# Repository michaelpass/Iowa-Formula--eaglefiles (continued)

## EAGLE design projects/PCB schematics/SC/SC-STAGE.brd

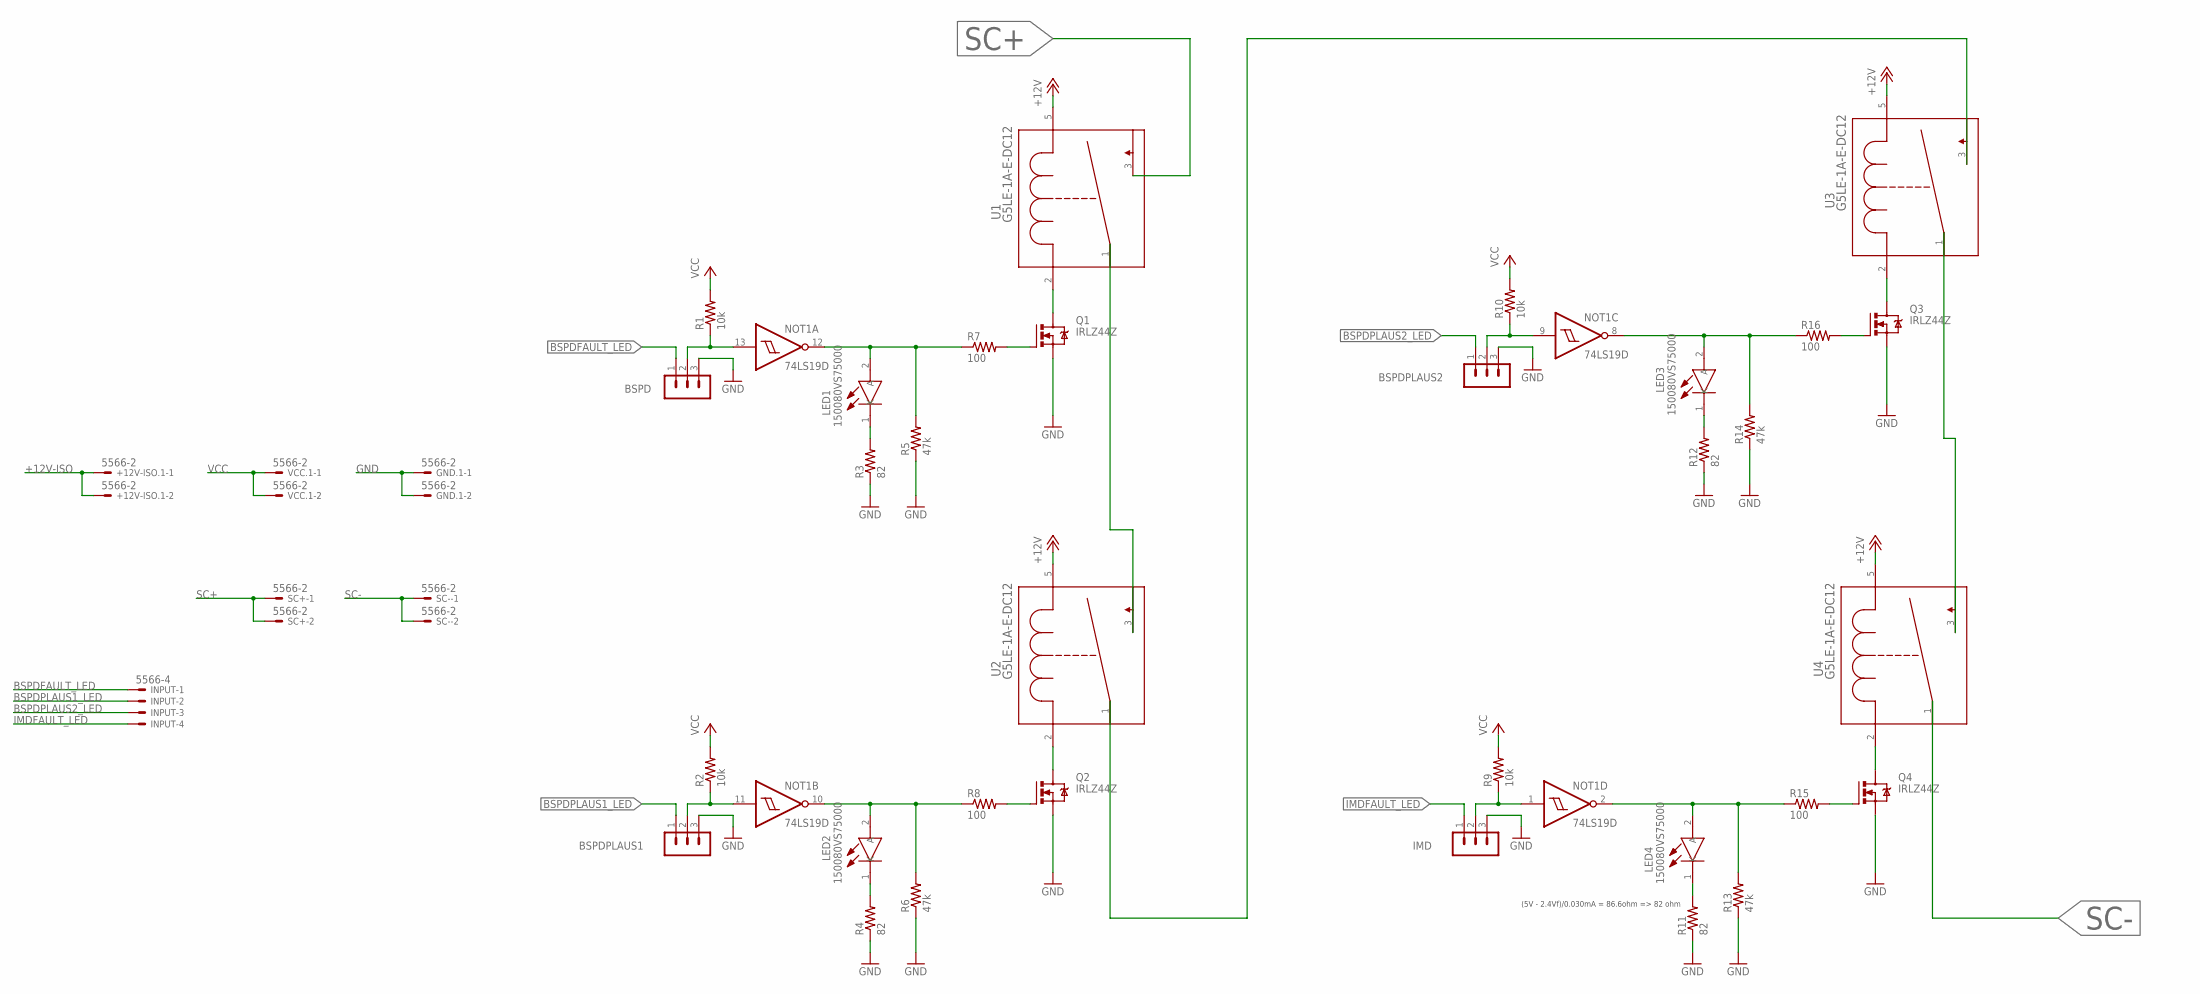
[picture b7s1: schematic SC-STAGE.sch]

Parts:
+12V-ISO.1: 5566-2
BSPD: MA03-1
BSPDPLAUS1, BSPDPLAUS2: MA03-1
GND.1: 5566-2
IMD: MA03-1
INPUT: 5566-4
LED1, LED2, LED3, LED4: 150080VS75000; LEDC2012X80N
NOT1: 74LS19D; SO14
Q1, Q2, Q3, Q4: IRLZ44Z; TO220BH
R1, R2, R9, R10: 10k; R0805
R3, R4, R11, R12: 82; R0805
R5, R6, R13, R14: 47k; R0805
R7, R8, R15, R16: 100; R0805
SC+: 5566-2
SC-: 5566-2
U1, U2, U3, U4: G5LE-1A-E-DC12
VCC.1: 5566-2

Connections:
+12V-ISO: +12V-ISO.1.1, +12V-ISO.1.2, U1.5 (4), U2.5 (4), U3.5 (4), U4.5 (4)
BSPDFAULT_LED: BSPD.1, INPUT.1
BSPDPLAUS1_LED: BSPDPLAUS1.1, INPUT.2
BSPDPLAUS2_LED: BSPDPLAUS2.1, INPUT.3
GND: BSPD.3, BSPDPLAUS1.3, BSPDPLAUS2.3, GND.1.1, GND.1.2, IMD.3, NOT1.7 (GND), Q1.S, Q2.S, Q3.S, Q4.S, R3.1, R4.1, R5.1, R6.1, R11.1, R12.1, R13.1, R14.1
IMDFAULT_LED: IMD.1, INPUT.4
LED4: LED4.1 (K), R11.2
unnamed: Q1.G, R7.2
unnamed: LED1.2 (A), NOT1.12 (O), R5.2, R7.1
unnamed: LED1.1 (K), R3.2
unnamed: Q1.D, U1.2 (1)
unnamed: Q2.G, R8.2
unnamed: LED2.2 (A), NOT1.10 (O), R6.2, R8.1
unnamed: LED2.1 (K), R4.2
unnamed: Q2.D, U2.2 (1)
unnamed: U1.1 (2), U2.3
unnamed: U3.1 (2), U4.3
unnamed: Q4.G, R15.2
unnamed: LED4.2 (A), NOT1.2 (O), R13.2, R15.1
unnamed: Q4.D, U4.2 (1)
unnamed: Q3.G, R16.2
unnamed: LED3.2 (A), NOT1.8 (O), R14.2, R16.1
unnamed: LED3.1 (K), R12.2
unnamed: Q3.D, U3.2 (1)
unnamed: U2.1 (2), U3.3
unnamed: BSPDPLAUS2.2, NOT1.9 (I), R10.1
unnamed: IMD.2, NOT1.1 (I), R9.1
unnamed: BSPDPLAUS1.2, NOT1.11 (I), R2.1
unnamed: BSPD.2, NOT1.13 (I), R1.1
SC+: SC+.1, SC+.2, U1.3
SC-: SC-.1, SC-.2, U4.1 (2)
VCC: NOT1.14 (VCC), R1.2, R2.2, R9.2, R10.2, VCC.1.1, VCC.1.2

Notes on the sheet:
(5V - 2.4Vf)/0.030mA = 86.6ohm => 82 ohm

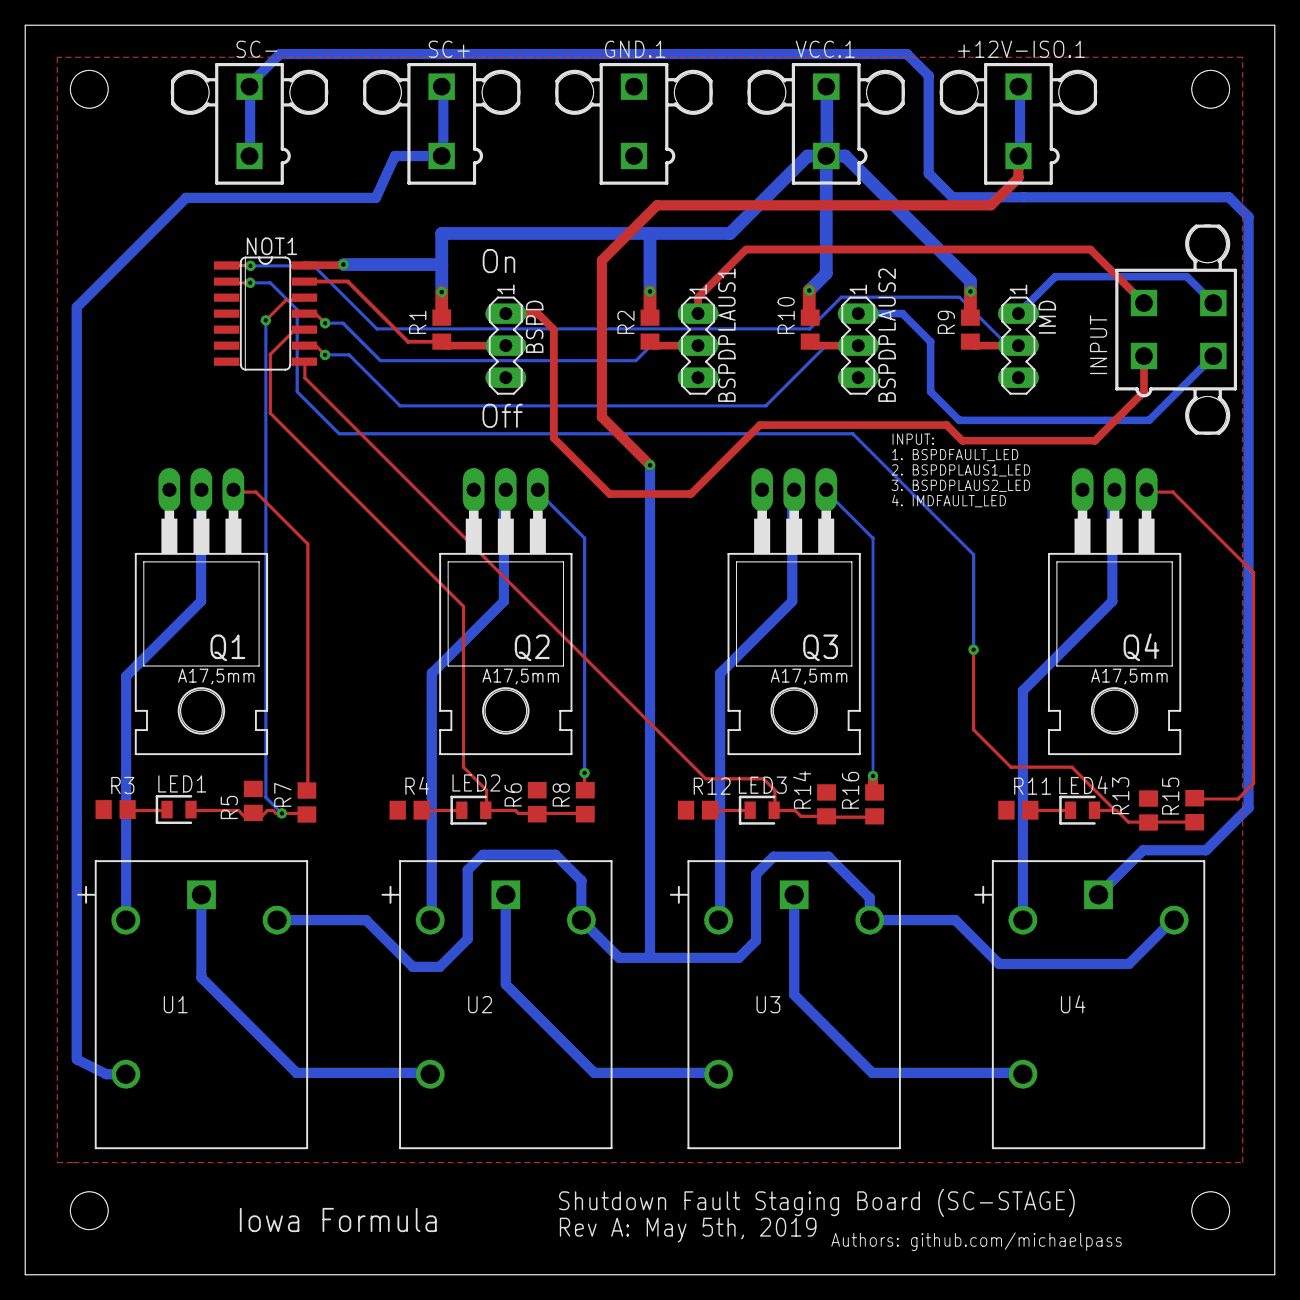
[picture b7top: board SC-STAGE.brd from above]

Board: 2 copper layers, 99.1 x 99.1 mm, 39 parts (0 on the bottom side), 32 nets.

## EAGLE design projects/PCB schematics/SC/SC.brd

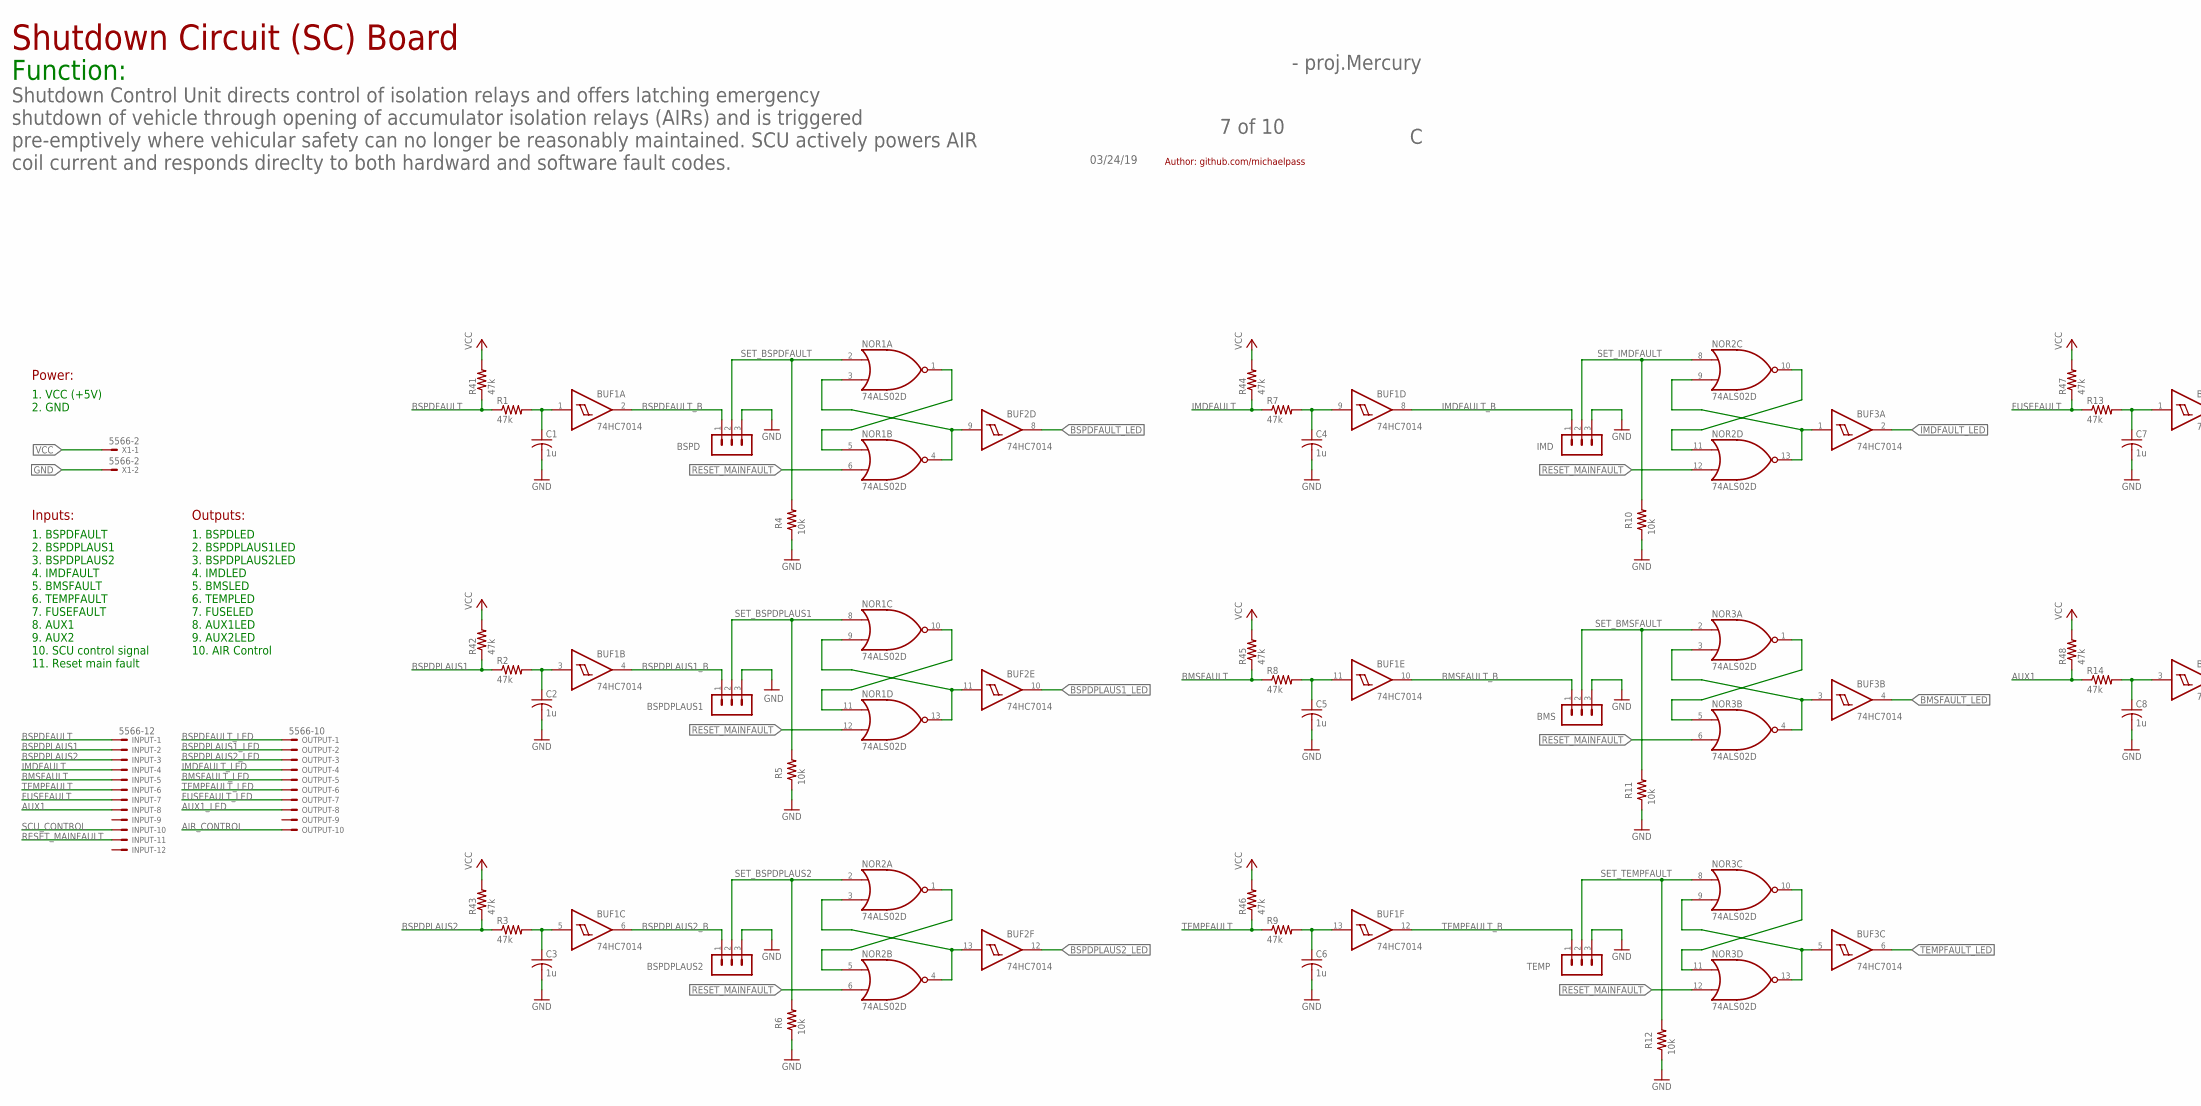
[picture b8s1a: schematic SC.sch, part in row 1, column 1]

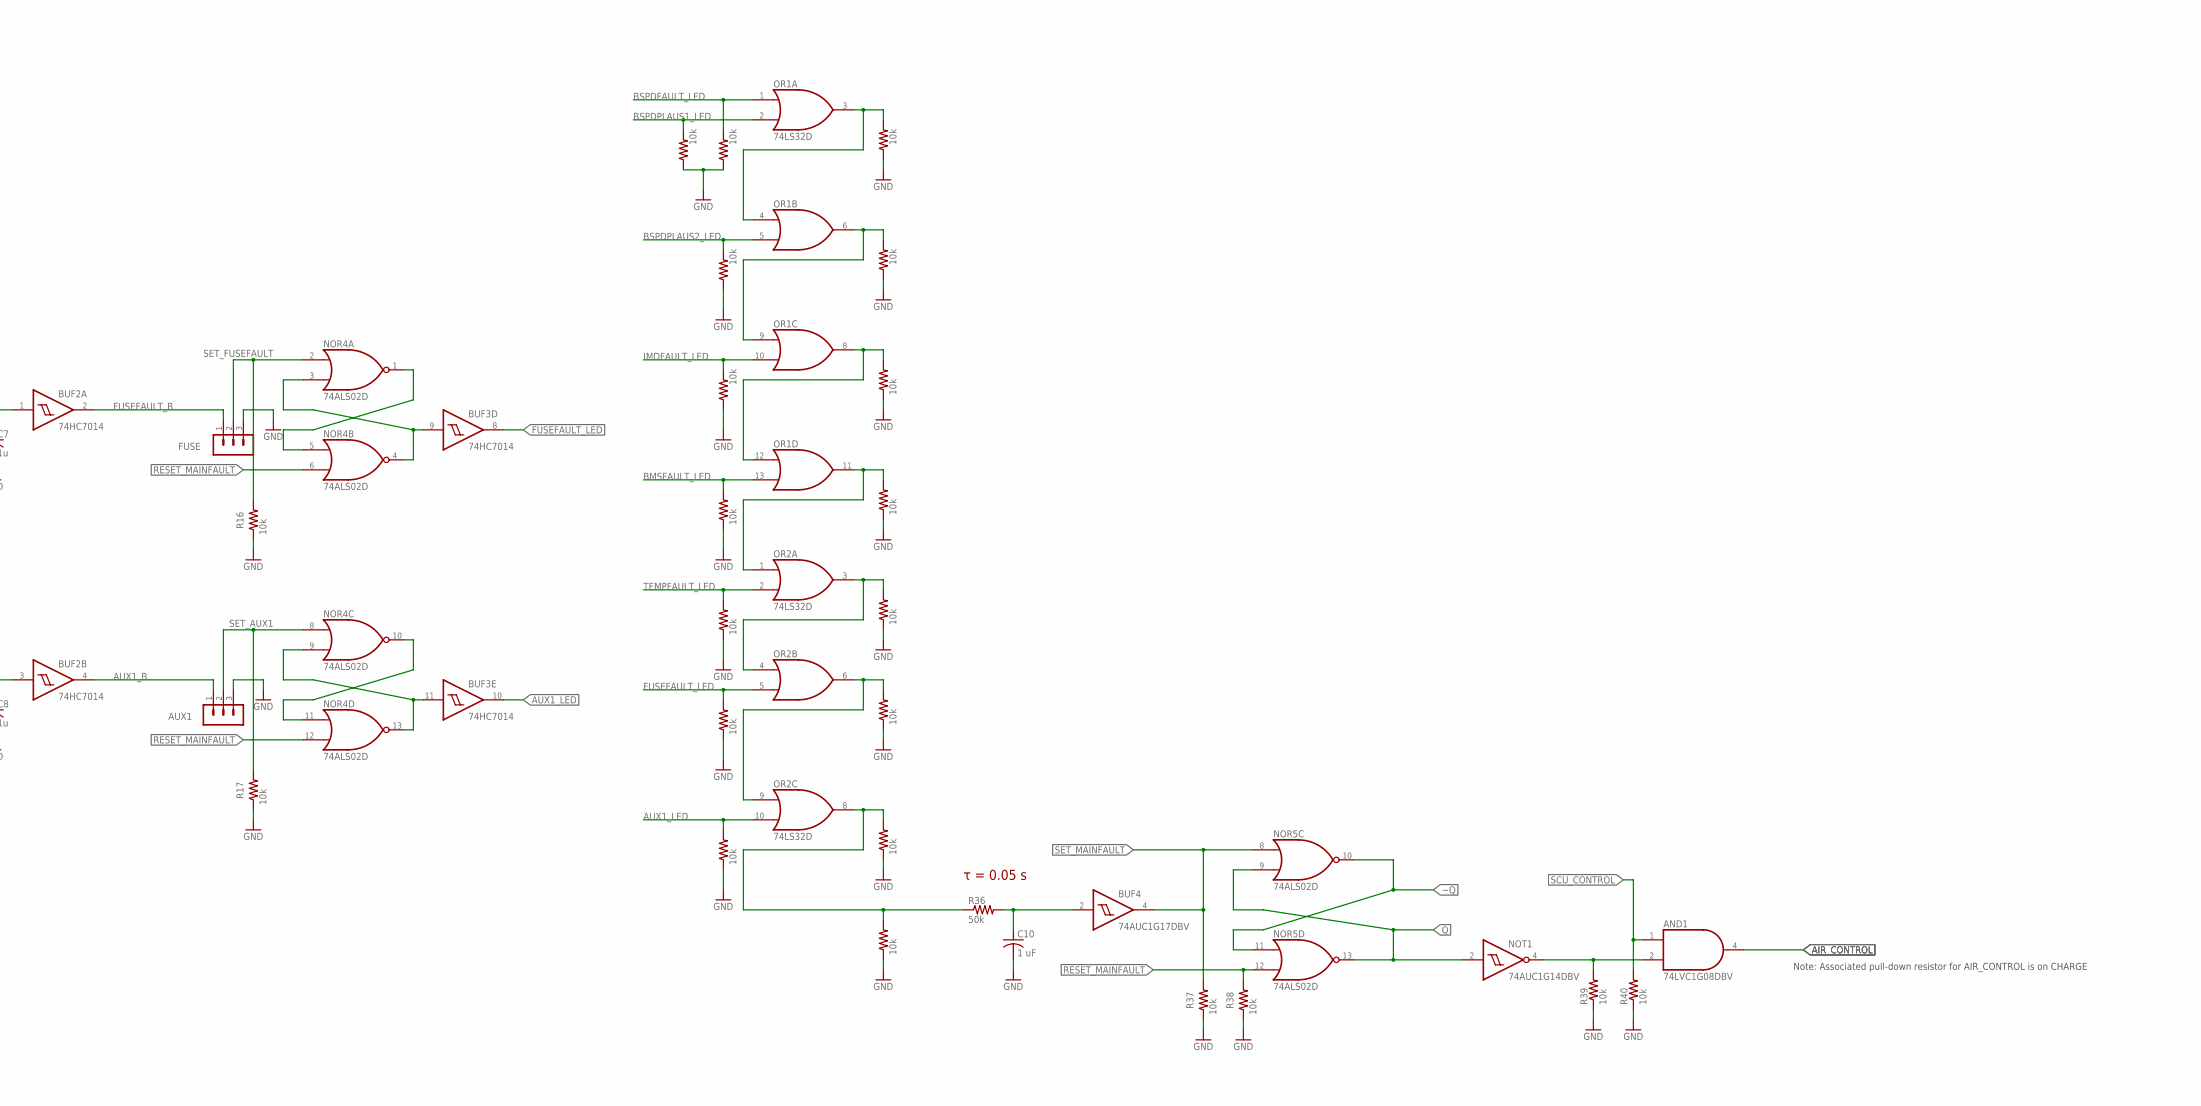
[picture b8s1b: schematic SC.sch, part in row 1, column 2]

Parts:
AND1: 74LVC1G08DBV; SOT23-5
AUX1: MA03-1
BMS: MA03-1
BSPD: MA03-1
BSPDPLAUS1, BSPDPLAUS2: MA03-1
BUF1, BUF2, BUF3: 74HC7014; SO14
BUF4: 74AUC1G17DBV; SOT23-5
C1, C2, C3, C4, C5, C6, C7, C8: 1u; C0805
C10: 1 uF; C0805
FUSE: MA03-1
IMD: MA03-1
INPUT: 5566-12
NOR1, NOR2, NOR3, NOR4, NOR5: 74ALS02D; SO14
NOT1: 74AUC1G14DBV; SOT23-5
OR1, OR2: 74LS32D; SO14
OUTPUT: 5566-10
R1, R2, R3, R7, R8, R9, R13, R14, R41, R42, R43, R44, R45, R46, R47, R48: 47k; R0805
R4, R5, R6, R10, R11, R12, R16, R17, R19, R20, R21, R22, R23, R24, R25, R26, R28, R29, R30, R31, R32, R33, R34, R35, R37, R38, R39, R40: 10k; R0805
R36: 50k; R0805
TEMP: MA03-1
X1: 5566-2

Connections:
AIR_CONTROL: AND1.4 (O), OUTPUT.10
AUX1: INPUT.8, R14.1, R48.1
AUX1_B: AUX1.1, BUF2.4 (O)
AUX1_LED: BUF3.10 (O), OR2.10 (I1), OUTPUT.8, R26.2
BMSFAULT: INPUT.5, R8.1, R45.1
BMSFAULT_B: BMS.1, BUF1.10 (O)
BMSFAULT_LED: BUF3.4 (O), OR1.13 (I1), OUTPUT.5, R23.2
BSPDFAULT: INPUT.1, R1.1, R41.1
BSPDFAULT_B: BSPD.1, BUF1.2 (O)
BSPDFAULT_LED: BUF2.8 (O), OR1.1 (I0), OUTPUT.1, R20.2
BSPDPLAUS1: INPUT.2, R2.1, R42.1
BSPDPLAUS1_B: BSPDPLAUS1.1, BUF1.4 (O)
BSPDPLAUS1_LED: BUF2.10 (O), OR1.2 (I1), OUTPUT.2, R19.2
BSPDPLAUS2: INPUT.3, R3.1, R43.1
BSPDPLAUS2_B: BSPDPLAUS2.1, BUF1.6 (O)
BSPDPLAUS2_LED: BUF2.12 (O), OR1.5 (I1), OUTPUT.3, R21.2
FUSEFAULT: INPUT.7, R13.1, R47.1
FUSEFAULT_B: BUF2.2 (O), FUSE.1
FUSEFAULT_LED: BUF3.8 (O), OR2.5 (I1), OUTPUT.7, R25.2
GND: AND1.3 (GND), AUX1.3, BMS.3, BSPD.3, BSPDPLAUS1.3, BSPDPLAUS2.3, BUF1.7 (GND), BUF2.7 (GND), BUF3.7 (GND), BUF4.3 (GND), C1.2, C2.2, C3.2, C4.2, C5.2, C6.2, C7.2, C8.2, C10.2, FUSE.3, IMD.3, NOR1.7 (GND), NOR2.7 (GND), NOR3.7 (GND), NOR4.7 (GND), NOR5.7 (GND), NOT1.3 (GND), OR1.7 (GND), OR2.7 (GND), R4.1, R5.1, R6.1, R10.1, R11.1, R12.1, R16.1, R17.1, R19.1, R20.1, R21.1, R22.1, R23.1, R24.1, R25.1, R26.1, R28.1, R29.1, R30.1, R31.1, R32.1, R33.1, R34.1, R35.1, R37.1, R38.1, R39.1, R40.1, TEMP.3, X1.2
IMDFAULT: INPUT.4, R7.1, R44.1
IMDFAULT_B: BUF1.8 (O), IMD.1
IMDFAULT_LED: BUF3.2 (O), OR1.10 (I1), OUTPUT.4, R22.2
unnamed: OR2.6 (O), OR2.9 (I0), R33.2
unnamed: OR2.8 (O), R34.2, R35.2, R36.1
unnamed: OR1.3 (O), OR1.4 (I0), R28.2
unnamed: BUF1.3 (I), C2.1, R2.2
unnamed: BUF1.5 (I), C3.1, R3.2
unnamed: BUF4.2 (I), C10.1, R36.2
unnamed: BUF1.9 (I), C4.1, R7.2
unnamed: AND1.2 (I1), NOT1.4 (O), R39.2
unnamed: BUF1.11 (I), C5.1, R8.2
unnamed: BUF1.13 (I), C6.1, R9.2
unnamed: OR1.6 (O), OR1.9 (I0), R29.2
unnamed: OR1.8 (O), OR1.12 (I0), R30.2
unnamed: OR1.11 (O), OR2.1 (I0), R31.2
unnamed: BUF2.1 (I), C7.1, R13.2
unnamed: BUF2.3 (I), C8.1, R14.2
unnamed: OR2.3 (O), OR2.4 (I0), R32.2
unnamed: BUF1.1 (I), C1.1, R1.2
Q: NOR5.9 (I1), NOR5.13 (O), NOT1.2 (I)
Q_AUX1: BUF3.11 (I), NOR4.9 (I1), NOR4.13 (O)
Q_BMSFAULT: BUF3.3 (I), NOR3.3 (I1), NOR3.4 (O)
Q_BSPDFAULT: BUF2.9 (I), NOR1.3 (I1), NOR1.4 (O)
Q_BSPDPLAUS1: BUF2.11 (I), NOR1.9 (I1), NOR1.13 (O)
Q_BSPDPLAUS2: BUF2.13 (I), NOR2.3 (I1), NOR2.4 (O)
Q_FUSEFAULT: BUF3.9 (I), NOR4.3 (I1), NOR4.4 (O)
Q_IMDFAULT: BUF3.1 (I), NOR2.9 (I1), NOR2.13 (O)
Q_TEMPFAULT: BUF3.5 (I), NOR3.9 (I1), NOR3.13 (O)
RESET_MAINFAULT: INPUT.11, NOR1.6 (I1), NOR1.12 (I1), NOR2.6 (I1), NOR2.12 (I1), NOR3.6 (I1), NOR3.12 (I1), NOR4.6 (I1), NOR4.12 (I1), NOR5.12 (I1), R38.2
SCU_CONTROL: AND1.1 (I0), INPUT.10, R40.2
SET_AUX1: AUX1.2, NOR4.8 (I0), R17.2
SET_BMSFAULT: BMS.2, NOR3.2 (I0), R11.2
SET_BSPDFAULT: BSPD.2, NOR1.2 (I0), R4.2
SET_BSPDPLAUS1: BSPDPLAUS1.2, NOR1.8 (I0), R5.2
SET_BSPDPLAUS2: BSPDPLAUS2.2, NOR2.2 (I0), R6.2
SET_FUSEFAULT: FUSE.2, NOR4.2 (I0), R16.2
SET_IMDFAULT: IMD.2, NOR2.8 (I0), R10.2
SET_MAINFAULT: BUF4.4 (O), NOR5.8 (I0), R37.2
SET_TEMPFAULT: NOR3.8 (I0), R12.2, TEMP.2
TEMPFAULT: INPUT.6, R9.1, R46.1
TEMPFAULT_B: BUF1.12 (O), TEMP.1
TEMPFAULT_LED: BUF3.6 (O), OR2.2 (I1), OUTPUT.6, R24.2
VCC: AND1.5 (VCC), BUF1.14 (VCC), BUF2.14 (VCC), BUF3.14 (VCC), BUF4.5 (VCC), NOR1.14 (VCC), NOR2.14 (VCC), NOR3.14 (VCC), NOR4.14 (VCC), NOR5.14 (VCC), NOT1.5 (VCC), OR1.14 (VCC), OR2.14 (VCC), R41.2, R42.2, R43.2, R44.2, R45.2, R46.2, R47.2, R48.2, X1.1
~Q: NOR5.10 (O), NOR5.11 (I0)
~Q_AUX1: NOR4.10 (O), NOR4.11 (I0)
~Q_BMSFAULT: NOR3.1 (O), NOR3.5 (I0)
~Q_BSPDFAULT: NOR1.1 (O), NOR1.5 (I0)
~Q_BSPDPLAUS1: NOR1.10 (O), NOR1.11 (I0)
~Q_BSPDPLAUS2: NOR2.1 (O), NOR2.5 (I0)
~Q_FUSEFAULT: NOR4.1 (O), NOR4.5 (I0)
~Q_IMDFAULT: NOR2.10 (O), NOR2.11 (I0)
~Q_TEMPFAULT: NOR3.10 (O), NOR3.11 (I0)

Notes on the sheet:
τ = 0.05 s
03/24/19
7 of 10
- proj.Mercury
Author: github.com/michaelpass
Function:
Shutdown Control Unit directs control of isolation relays and offers latching emergency shutdown of vehicle through opening of accumulator isolation relays (AIRs) and is triggered pre-emptively where vehicular safety can no longer be reasonably maintained. SCU actively powers AIR coil current and r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
Shutdown Circuit (SC) Board
Inputs:
1. BSPDFAULT 2. BSPDPLAUS1 3. BSPDPLAUS2 4. IMDFAULT 5. BMSFAULT 6. TEMPFAULT 7. FUSEFAULT 8. AUX1 9. AUX2 10. SCU control signal 11. Reset main fault
Outputs:
1. BSPDLED 2. BSPDPLAUS1LED 3. BSPDPLAUS2LED 4. IMDLED 5. BMSLED 6. TEMPLED 7. FUSELED 8. AUX1LED 9. AUX2LED 10. AIR Control
Power:
1. VCC (+5V) 2. GND
Note: Associated pull-down resistor for AIR_CONTROL is on CHARGE

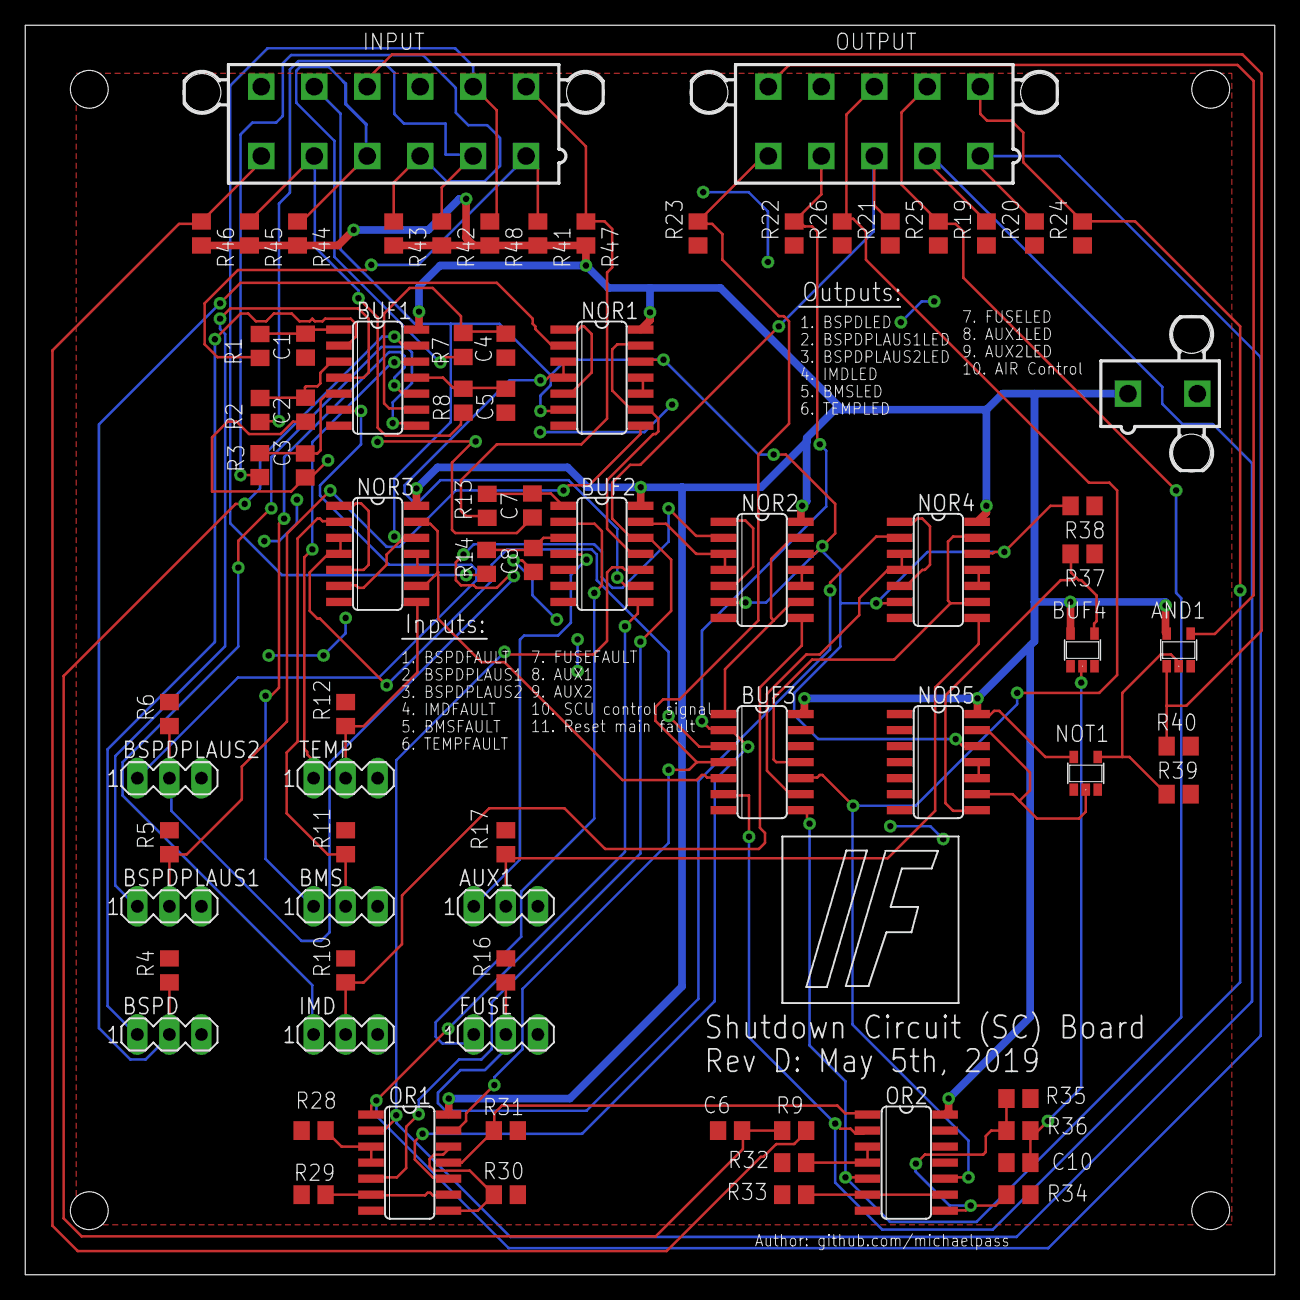
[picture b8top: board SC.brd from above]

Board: 2 copper layers, 99.1 x 99.1 mm, 78 parts (0 on the bottom side), 73 nets.

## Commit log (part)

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2019-02-23 Compatibility revision of .gitignore for cross-platform compatibility. Reset of repo history
2019-04-01 SC - Rev A; First PCB revision complete.
    This marks the first draft of the SC board.
    Parts have been laid out and initial routing completed through
    extensive use of autorouter.
2019-04-01 SC - Added component numbers/names.
    Silkscreen was initially missing component names.
    As many of the original components were resistors/capacitors,
    Values were preferred.
    However, standard board markup convention requires that part numbers
    be given instead.
    Note: Part numbers are given on EAGLE layer tNames, whereas values
2019-04-01 SC - Silkscreen tidy.
    Many silkscreen labels were previously unreadable.
    This commit consisted of moving labels into readable positions
    without as much via obstruction.
2019-04-01 SC - Removed LATCH.
    LATCH board schematic kept around for Electronic Systems Form (ESF)
    All functionality was absorbed through multiple latch circuits added
    through this commit.
2019-04-01 TSMPC - Initial draft (WIP).
    Non-working commit of TSMPC.
    Done simply to show possible board layout.
2019-04-01 PROJ - Deleted duplicate directories.
    $PATH confusion between Windows and POSIX systems lead to multiple nested entries of repository in files. These have been deleted and repo has been consolidated properly.
2019-04-01 SC - Rev C; SC70 -> SOT23.
    For single logic gate components, SC70 was initially chosen.
    These packages proved too small to hand-solder.
    All SC70 packages have been refactored to SOT23.
    SparkFun DRC's added in for additional manufacturability.
2019-04-01 TSALC - Initial build.
    Initial build done by Anshuman.
    TSALC is still WIP.
    TSALC work must be continued on another branch.
2019-04-01 PROJ - Workstation modified files.
    Git history had become polluted with multiple trivial commits.
    Git branching/merging policy will now be followed through GitHub.
    WLS system set up. Anshuman's git history caught up.
    All systems under management have now been merged at this common commit.
2019-04-01 Backlink to CADLAB.io has been added.
2019-04-01 PROJ - Readme modified.
    GitHub is desired to be used as a central project hub for distributing these files.
    Therefore, README.me has been updated to include better explanation of how to install project files. Team logo added to base of repo. TODO: Add to image to GitHub hosting.
2019-04-01 BSPD - Schematic finalized.
    BSPD schematic needed final refactoring for parts.
    Adjustable threshold settings have been put in for plausibility checks
    using resistor arrays.
    Squashed - BSPD - Removed BSPD.brd.
    Too much work will be required to refactor this board.
    It's currently 10 inches long.
2019-04-01 BSPD - Hand routing complete.
    Proceding with auto routing.
    Squashed - BSPD - Initial routing.
    Routing underway. Ground pour chosen. Routing easy choices before attempting autorouting.
2019-04-01 BSPD - Auto-routing complete.
    Performed autorouting. Results generally good. Must correct for ground islands left.
    Must touch up board clearances. BSPD otherwise done.
2019-04-01 BSPD - Rev A; Gerber files.
    Initial board revisions complete. This board represents a working draft. GERBER files have been generated. Please review.
2019-04-02 PROJ - .gitignore includes renumsch.scr
    Whenever the renumber sheet ULP is used, an additional file called renumsch.scr is created. This file occasionally deletes itself, adding unneeded noise to changelog.
2019-04-02 PROJ - Added shorts.lbr.
    Unforunately, EAGLE does not allow for one netlist with multiple names. This is consistent with bringing in two signals together on a PCB, and directly connecting them. There are two solutions for th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
    - Add additional silkscreen and text information to schematic/PCB respectively to show that although there is one common net name for two connectors, they should breakout to different parts of the ci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
    - Use a sort of 'hack' by creating a part which directly shorts on a PCB. This second option produces a more obvious netlist and tidier schematic, but will set off DRC rules checks that must be manua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
    I'll try out the former method to begin with.
    The b
2019-04-02 PROJ - Updated PF1262.lbr
    Previous PF1262.lbr for precharge/discharge resistors was not compatible with ordered Riedon parts.
    Unlike all other TO-126 packages, Riedon's resistors are 2 legged. Upon further inspection, this stated footprint is roughly compatible with the standard TO-126 package, with the middle terminal leg 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
    Two versions of this package were created. One with, and one with/out heatsink.
2019-04-08 PROJ - Renamed library folders. Added con-MATE-N-LOK.
    Custom library files were not showing up upon refresh in EAGLE. The best guess for why this behavior was occuring was that EAGLE only goes one folder deep in looking for matching library names. So, a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
    Additionally, a con-MATE-N-LOK library has been added and will be added on as parts are needed. Please check for commits made on master branch for these.
2019-04-08 PROJ - Added 2P(90deg and vert) connectors to con-MATE lbr.
2019-04-11 PROJ - Arduino-clone.lbr
2019-04-11 PROJ - .gitignore; Added -0 for ignored directories in projects.
2019-04-11 PROJ - .gitignore; Globbing notation fix.
2019-04-11 FUSE - Pull request #4.
    Squash - FUSE - PR#4 changes.
    Minor changes made in trace placement.
2019-04-11 FUSE - Rev A.
    Pull request #4 completed.
    GERBER files for Rev. A created.
2019-04-11 TSMPC - Initial revisions from pull request #3.
    Many changes were needed from Anshuman's initial pull request version. Half of the necessary changes have been made here. Connectors must be added. I believe we should also add in a seperate GND boar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
2019-04-11 TSMPC - Additional revisions for pull request #3.
    Final revisions (apart from connectors and creation of simple GND board) have been done and are ready for review by Anshuman Sahu (and selection of HV connectors)
    Squash - TSMPC - Fixed missing connection as per @rgoedken, PR#3.
    Squash - TSMPC - Added connectors. PR#3 suggestions. Pending approval.
2019-04-11 TSMPC - GLV, Rev A.
    Added in two connectors for chassis connections. X2 goes to TSMP GND connector. Other connector gives 6 access points to ground.
    Squash - TSALC - GLV; Fixed mounting holes.
2019-04-11 TSMPC - Initial revision.
    Completed board, minus the connector. Still needs verification from @michaelpass .
2019-04-11 TSMPC - Rev A.
    Pull request #3 completed.
    GERBER files generated for both TS and GLV boards.
2019-04-11 CHARGE - PR#2 requests made per @rgoedken.
    - Third mosfet added in.
    - Connector expanded to 8 pin
    - AIR+/- added in
    - Short device used to handle connections to power rail
    - 5A fuse added in. 885 makes 5A.
    - 100 ohm gate resistors added into three mosfets.
2019-04-11 CHARGE - Rev A.
    Pull request #2 completed.
    GERBER files created for Rev. A.
2019-04-11 PROJ - EKXF451ELL100MJ20S.lbr.
    Added electrolytic capacitor for 450VDC rated cap.
2019-04-11 TSALC - TS initial revision.
    Squash - TSALC - Added current limited resistors to OK1.
    Squash - TSALC - Hand routing complete.
    GLV components moved over to a separate board with minimal connections left on TS part. Distance explicitly shown on silkscreen. Will require conformal coating to fall in specification.
    All high volt connectors are on the top of the board (vertical connectors chosen, as this will occur outside of accumulator container.)
    Will tidy silkscreen and check for DRC errors.
    Squash - TSALC - Silkscreen additions.
2019-04-11 TSALC - TS; Rev A.
    Adding in silkscreen markings.
    Board has TS and GLV markings separated by 8.26mm. This is the limit imposed by the optocoupler. The rules state that optocouplers are exempt. However, they will likely consider any copper leading up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
    TSALC - TS; Rev A. Pull request #5.
    TSALC boards now ready for pull request review.
2019-04-11 Minor board update
    Cleared up come wiring conflicts
    Board Schematic Update
    555 Timer Circuit changed accordingly.
    (ref. https://www.allaboutcircuits.com/tools/555-timer-astable-circuit/)
    Flash Frequency = 4.80 Hz
    Duty Cycle = 66.67%
2019-04-11 TSALC - Capacitors updated with new EDA files.
    Capacitors now current.
2019-04-11 PROJ - L78L08ABD13TR added to IowaFormula.lbr.
2019-04-12 PROJ - SparkFun.lbr and microbuilder.lbr
    Adding old SparkFun library (deprecated, but used by previous open source schematics), and microbuilder library. This will allow for easier creation of Arduino/Adafruit PCB machine pin sockets.
2019-04-22 TSALC - TS; Rev A.
    Adding in silkscreen markings.
    Board has TS and GLV markings separated by 8.26mm. This is the limit imposed by the optocoupler. The rules state that optocouplers are exempt. However, they will likely consider any copper leading up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
    TSALC - TS; Rev A. Pull request #5.
    TSALC boards now ready for pull request review.
    ---SQUASH---
    TSALC - Capacitors updated with new EDA files.
2019-04-22 TSALC - Initial draft.
    Cleared up come wiring conflicts
    Board Schematic Update
    555 Timer Circuit changed accordingly.
    (ref. https://www.allaboutcircuits.com/tools/555-timer-astable-circuit/)
    Flash Frequency = 4.80 Hz
    Duty Cycle = 66.67%
2019-04-22 ACCUM - Rev A.
2019-04-22 ACCUM - Added POWER board.
    ACCUM - POWER and SIGNAL complete.
    Two separate boards have been created. One for Powerex, and one for signal sampling.
2019-04-22 CAN - Initial draft.
    Vertical connectors chosen. Several options should be compliant with this PCB footprint.
2019-04-23 ACCUM - BOM created.
2019-04-23 POWER - Initial drafts.
    Adding in initial place holders for DCDC, 5V, and 12V. Completed most of TEMP.
2019-04-23 RTDS - Initial draft.
    Arduino Nano and SoundFX boards added.
    Must complete wiring.
2019-04-23 RTDS - Intial commit.
    Board not in draft state yet. Committing out to add in parts to master.
2019-04-23 PROJ - Added DISCHARGE.
2019-04-23 PROJ - Added SC-STAGE.
    We'll need to add in extra power-staging for all of our latching faults.
    This can be easily achieved through MOSFETs. So, instead of using logic to filter out our control signal in combinational logic, we also use these individual latching faults to break the coil current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
2019-04-24 PROJ - Added test file.
2019-04-24 TSAL - Minor fixes.
2019-04-24 TSAL - Added in FUSE to HV sense line.
    Added in FUSE and removed redundant tantalum capacitors.
2019-04-24 PROJ - Added IMD, OUTPUT.
    Additional changes made to INPUT.
    OUTPUT board added for ECU/motor controller signal processing.
    IMD added for IMD fuse board. Rules may require fusing IMD. Might as well.
2019-04-29 TEMP - Energus components added in.
2019-04-30 TEMP - Initial board placement; Horizontal redo.
2019-04-30 TEMP - Final routing.
2019-04-30 SC - Hand routing. Ready for autorouter.
2019-04-30 SC - Final revision D.
2019-04-30 TSMPC - Board 3900milx3900mil redo.
2019-04-30 RTDS - Rev A.
2019-04-30 RTDS - R L audio wiring to amplifiers.
2019-05-02 POWER - DC DC 90% done.
2019-05-02 POWER - DCDC Rev A.
2019-05-02 POWER - DCDC; Copper pour adjustment.
2019-05-02 SC - Stage initial placement.
2019-05-03 ACCUM - Added IMD fuses.
2019-05-03 CAN - Further distancing of CAN_H/CAN_L routing.
2019-05-04 POWER - 12V5V 90%
2019-05-04 POWER - 12V5V revisions.
2019-05-04 POWER - DCDC changes w/ Ryan.
2019-05-04 RTDS + TSAL Board update
    Minor board & schematic errors corrected
2019-05-04 AMAR - 12V5V initial routing.
2019-05-04 POWER - 12V5V Rev A.
2019-05-05 PROJ - Silkscreen modifications - 50%.
2019-05-05 PROJ - Final pre-purchase revisions (4 boards still in progress.)
2019-05-05 PROJ - Mounting holes fixed to 200mil x 200mil away from edges for universal extra-Accumulator-based mounted.
2019-05-05 PROJ - Rgoedken split TSAL signal resistors into smaller resistors for voltage divider; current voltage divider split would have dropped too high a voltage against previous resistor's rated voltage.
2019-05-05 PROJ - Gerber file addition
    Added folder for most recent gerber files. Note: Gerber files also stored in parent directories.
